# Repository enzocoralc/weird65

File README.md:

# weird65
 small 40% with num and F rows

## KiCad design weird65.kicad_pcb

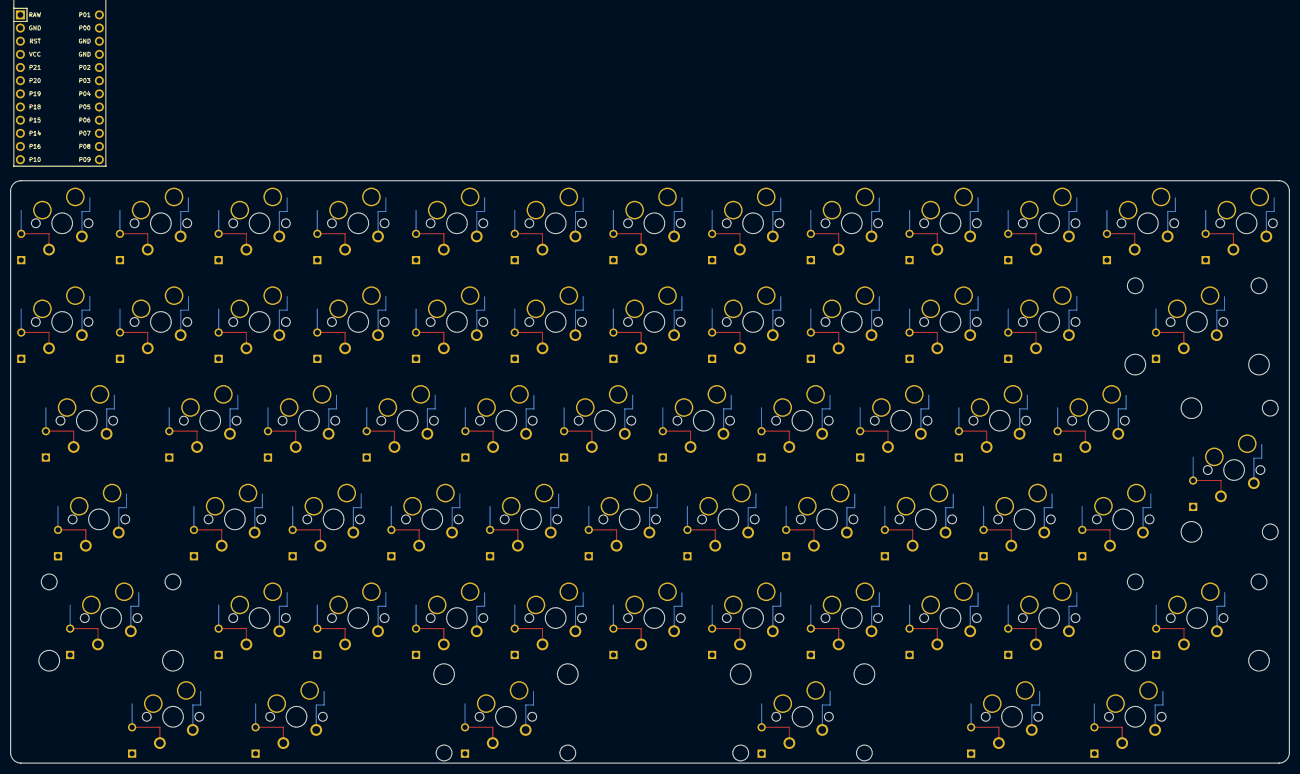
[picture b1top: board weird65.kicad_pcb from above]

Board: 2 copper layers, 246.8 x 112.4 mm, 72 parts (0 on the bottom side), 18 nets, no tracks yet.

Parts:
MCU1: ProMicro
SW1, SW2, SW3, SW4, SW5, SW6, SW7, SW8, SW9, SW10, SW11, SW12, SW13, SW14, SW15, SW16, SW17, SW18, SW19, SW20, SW21, SW22, SW23, SW24, SW25, SW27, SW28, SW29, SW30, SW31, SW32, SW33, SW34, SW35, SW36, SW37, SW38, SW39, SW40, SW41, SW42, SW43, SW44, SW45, SW46, SW47, SW48, SW49, SW53, SW54, SW55, SW56, SW57, SW59, SW61, SW62, SW63, SW65, SW67, SW68, SW69, SW71, SW72, SW73, SW74: SW_Diode; MX_solder-hotswap-flippedPins
stab1, stab2, stab3, stab4, stab5, stab6: Stabilizer_Cherry_MX_2.00u

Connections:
col1: SW1.1, SW14.1, SW27.1, SW28.1, SW53.1, SW54.1
col2: SW2.1, SW15.1, SW29.1, SW30.1, SW55.1, SW56.1
col3: SW3.1, SW16.1, SW31.1, SW32.1, SW57.1
col4: SW4.1, SW17.1, SW33.1, SW34.1, SW59.1
col5: SW5.1, SW18.1, SW35.1, SW36.1, SW61.1, SW62.1
col6: SW6.1, SW19.1, SW37.1, SW38.1, SW63.1
col7: SW7.1, SW20.1, SW39.1, SW40.1, SW65.1
col8: SW8.1, SW21.1, SW41.1, SW42.1, SW67.1, SW68.1
col9: SW9.1, SW22.1, SW43.1, SW44.1, SW69.1
col10: SW10.1, SW23.1, SW45.1, SW46.1, SW71.1, SW72.1
col11: SW11.1, SW24.1, SW47.1, SW48.1, SW73.1, SW74.1
col12: SW12.1, SW25.1, SW49.1
row1: SW1.2, SW2.2, SW3.2, SW4.2, SW5.2, SW6.2, SW7.2, SW8.2, SW9.2, SW10.2, SW11.2, SW12.2, SW13.2
row2: SW14.2, SW15.2, SW16.2, SW17.2, SW18.2, SW19.2, SW20.2, SW21.2, SW22.2, SW23.2, SW24.2, SW25.2
row3: SW27.2, SW29.2, SW31.2, SW33.2, SW35.2, SW37.2, SW39.2, SW41.2, SW43.2, SW45.2, SW47.2, SW49.2
row4: SW28.2, SW30.2, SW32.2, SW34.2, SW36.2, SW38.2, SW40.2, SW42.2, SW44.2, SW46.2, SW48.2
row5: SW53.2, SW55.2, SW57.2, SW59.2, SW61.2, SW63.2, SW65.2, SW67.2, SW69.2, SW71.2, SW73.2
row6: SW54.2, SW56.2, SW62.2, SW68.2, SW72.2, SW74.2

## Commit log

2022-11-12 moved the promicro to the left
2022-11-12 added xiao, Shift registers and wired it
    DRC is giving a lot of errors due to the switches footprint. There are a few more errors
2022-11-13 added a bunch of stuff
    fixed the xiao and switch footprints. Added a folder with the used footprints
2022-11-13 added the xiao symbol
2022-11-15 added the KLE
2022-11-16 backups changed
2022-11-18 added backup files
2022-11-20 reordered the files and added the V2 KLE revisions
2022-12-03 added a zip file
2022-12-03 added ANSI/ISO compatibility
2024-09-25 Update README.md
    fixed typo
